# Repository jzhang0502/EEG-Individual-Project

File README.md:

# Electroencephalogram Device with Integrated Signal Processing for Daily Operations
## Author:
Yiyou Zhang

## About The Project 🧠:
This project aims to create an Electroencephalogram (EEG) system that records and utilises the user's neuroactivities, enabling the user to remotely activate a coffee machine with only the thoughts of wanting more coffee. It is advised, however, to consume caffeine in a responsible and moderate quantity.

## Milestones:
- [ ] Complete building functional EEG device
    - [x] Research on fundamental mechanisms of an EEG headset
    - [x] Identify and sketch out primary circuit elements
    - [x] Create schematic of EEG device on LTspice
    - [x] Source all required circuit components on DigiKey
    - [x] Complete project symbol library and overall schematic on KiCad
    - [ ] Complete PCB design on KiCad
    - [ ] Finish assembling all components on custom PCB and test out EEG device
- [ ] Perform signal processing and analysis on EEG data
- [ ] Create models capable of recognising specific EEG activities

## License:

Distributed under the MIT License. See `LICENSE.txt` for more information.

<p align="right">(<a href="#readme-top">back to top</a>)</p>

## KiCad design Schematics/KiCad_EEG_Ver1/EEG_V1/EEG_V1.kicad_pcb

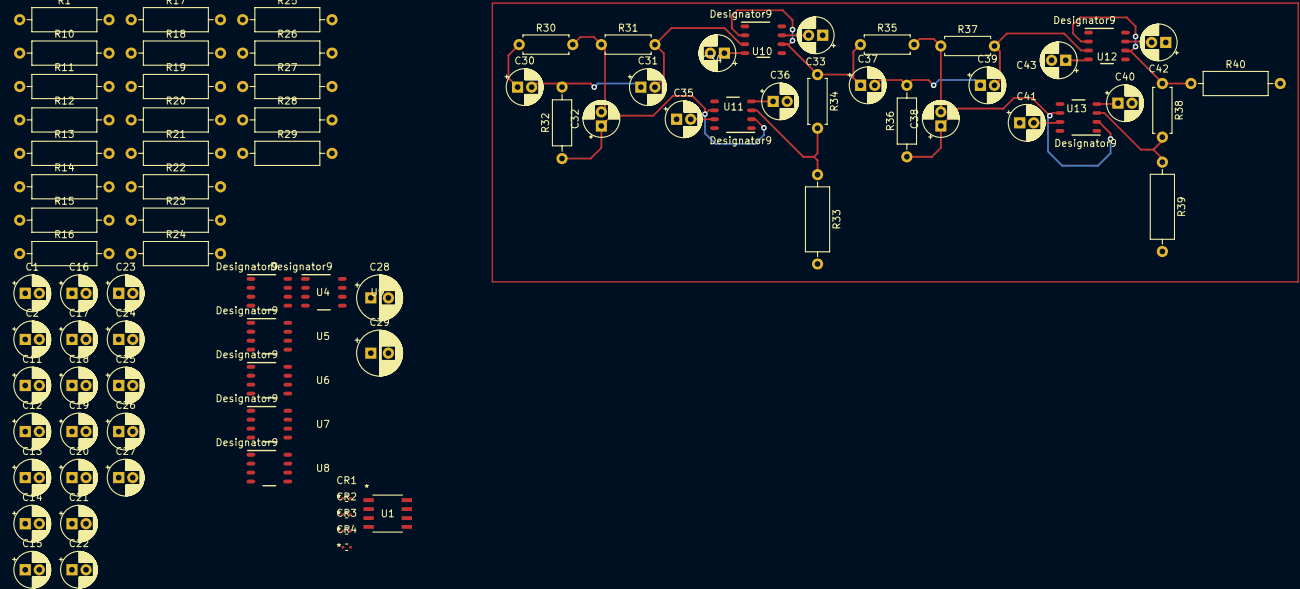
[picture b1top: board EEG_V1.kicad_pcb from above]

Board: 2 copper layers, 82 parts (0 on the bottom side), 35 nets.

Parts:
C1, C2, C14, C15, C16, C17, C19, C20, C22, C23, C24, C25, C26, C27, C30, C31, C33, C34, C35, C36, C37, C39, C40, C41, C42, C43: 0.1u; CP_Radial_D5.0mm_P2.00mm
C11, C21: 33n; CP_Radial_D5.0mm_P2.00mm
C12, C13, C18: 5.6n; CP_Radial_D5.0mm_P2.00mm
C28, C29: 10u; CP_Radial_D6.3mm_P2.50mm
C32, C38: 0.2u; CP_Radial_D5.0mm_P2.00mm
CR1, CR2, CR3, CR4: D5V0F1U2S9-7; CR_0F1U2S9-7_DIO
R1: 2k; R_Axial_DIN0309_L9.0mm_D3.2mm_P12.70mm_Horizontal
R10, R11, R26: 4.99k; R_Axial_DIN0309_L9.0mm_D3.2mm_P12.70mm_Horizontal
R12, R13: 22k; R_Axial_DIN0309_L9.0mm_D3.2mm_P12.70mm_Horizontal
R14, R15, R16, R18, R25, R28, R33, R39, R40: 10k; R_Axial_DIN0309_L9.0mm_D3.2mm_P12.70mm_Horizontal
R17: 499k; R_Axial_DIN0309_L9.0mm_D3.2mm_P12.70mm_Horizontal
R19, R22: 100k; R_Axial_DIN0309_L9.0mm_D3.2mm_P12.70mm_Horizontal
R20: 1.8k; R_Axial_DIN0309_L9.0mm_D3.2mm_P12.70mm_Horizontal
R21: 5.6k; R_Axial_DIN0309_L9.0mm_D3.2mm_P12.70mm_Horizontal
R23, R24, R27: 2.37k; R_Axial_DIN0309_L9.0mm_D3.2mm_P12.70mm_Horizontal
R29: R; R_Axial_DIN0309_L9.0mm_D3.2mm_P12.70mm_Horizontal
R30, R31, R35, R37: 32k; R_Axial_DIN0207_L6.3mm_D2.5mm_P7.62mm_Horizontal
R32, R36: 16k; R_Axial_DIN0207_L6.3mm_D2.5mm_P10.16mm_Horizontal
R34, R38: 250; R_Axial_DIN0207_L6.3mm_D2.5mm_P7.62mm_Horizontal
U1: INA819IDGK; INA819ID
U4, U5, U6, U7, U8, U9, U10, U11, U12, U13: OPA172IDR

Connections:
/Vout1: C21.1, R19.1, R20.2, U1.7, U6.3 (IN+)
DRL_in: R12.1, R13.1, U5.3 (IN+)
EEG_out: R28.2, U9.6 (OUT)
Inv_Summing_Amp_in: R23.2, R24.1, R27.1, U8.2 (IN-)
unnamed: C11.1, C12.1, CR2.2, CR4.1, R10.2, R15.1
unnamed: C11.2, C13.2, CR1.2, CR3.1, R11.2, R16.1
unnamed: C30.2, C31.1, R32.2
unnamed: C32.2, R30.2, R31.1
unnamed: C37.2, C39.1, R36.2
unnamed: C38.2, R35.2, R37.1
unnamed: R1.1, R12.2, U1.2 (Rg)
unnamed: R1.2, R13.2, U1.3 (Rg)
unnamed: R24.2, R25.2, R26.2
unnamed: R15.2, U1.4 (+)
unnamed: R16.2, U1.1 (-)
unnamed: C18.1, R14.2, R17.1, U4.2 (IN-)
unnamed: C18.2, R17.2, R18.1, U4.6 (OUT)
unnamed: R14.1, U5.2 (IN-), U5.6 (OUT)
unnamed: C21.2, R19.2, R21.1, U6.6 (OUT)
unnamed: R21.2, R22.1, U7.2 (IN-)
unnamed: R22.2, R23.1, U7.6 (OUT)
unnamed: R27.2, R29.1, U8.6 (OUT)
unnamed: R28.1, R29.2, U9.2 (IN-)
unnamed: C31.2, R31.2, U10.3 (IN+)
unnamed: C37.1, R34.1, R35.1, U10.2 (IN-), U10.6 (OUT)
unnamed: R33.1, R34.2, U11.3 (IN+)
unnamed: C32.1, R32.1, U11.2 (IN-), U11.6 (OUT)
unnamed: C39.2, R37.2, U12.3 (IN+)
unnamed: R38.1, R40.1, U12.2 (IN-), U12.6 (OUT)
unnamed: R38.2, R39.1, U13.3 (IN+)
unnamed: C38.1, R36.1, U13.2 (IN-), U13.6 (OUT)
Notch_in: C30.1, R30.1
Notch_out: C1.1, C2.2, C12.2, C13.1, C14.1, C15.2, C16.1, C17.2, C19.1, C20.2, C22.1, C23.2, C24.1, C25.2, C26.2, C27.1, C28.2, C29.1, C33.1, C34.2, C35.1, C36.2, C40.2, C41.1, C42.1, C43.2, R20.1, R25.1, R33.2, R39.2, R40.2, U1.6 (Ref), U4.3 (IN+), U7.3 (IN+), U8.3 (IN+), U9.3 (IN+)
V++: C1.2, C14.2, C16.2, C19.2, C22.2, C24.2, C27.2, C29.2, C33.2, C35.2, C41.2, C42.2, CR1.1, CR2.1, R26.1, U1.8 (V+), U4.7 (V+), U5.7 (V+), U6.7 (V+), U7.7 (V+), U8.7 (V+), U9.7 (V+), U10.7 (V+), U11.7 (V+), U12.7 (V+), U13.7 (V+)
V--: C2.1, C15.1, C17.1, C20.1, C23.1, C25.1, C26.1, C28.1, C34.1, C36.1, C40.1, C43.1, CR3.2, CR4.2, U1.5 (V-), U4.4 (V-), U5.4 (V-), U6.4 (V-), U7.4 (V-), U8.4 (V-), U9.4 (V-), U10.4 (V-), U11.4 (V-), U12.4 (V-), U13.4 (V-)

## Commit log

2024-01-02 Create README.md
    Added initial README file to set up repository
2024-01-02 Created .gitignore file for repo
2024-01-02 Added MIT LICENSE for repo
2024-01-02 Initial update to main README.txt
    Added project details, listed milestones and nested tasks
2024-01-02 Updated main README.txt milestone progress
    Completed researching, and sketching first overall circuit schematic on LTspice
2024-01-02 Initial sketch of EEG device gain stages
    The sketch includes the following:
    - 2x9V battery power source
    - INA819 inst amp with 21 gain
    - Non-inv op amp with 55.95 gain
    - Non-inv op amp with 18.86 gain
    - Total gain 22156
2024-01-02 Updated EEG_Schematic_LT
    Following additions:
    - Driven right leg circuit with gain 50
    - Added capacitor on stage 2 non-inv op amp as low-pass filter with Fc = 48Hz
    - Additional descriptions on circuit blocks
2024-01-02 Updated EEG_Schematic_LT.asc
    Following additions and alterations:
    - Added voltage source as "Electrode" that simulates electrode readings
    - Connected all parts of EEG circuit
    - Added optional high-pass filter to connect to inst amp
    - Changed inst amp gain to 22.10
    - Changed stage 2 non-inv op amp gain to 56.56
2024-01-02 Updated EEG_Schematic_LT.asc
    Following changes:
    - Changed stage 3 non-inv op amp gain to 17.86
    - Total gain is now 22322.82
2024-01-02 Updated EEG_Schematic_LT.asc
    Following changes:
    - Additional documentation to explain every circuit element
    - Stage 1 INA819 inst amp gain is 22.10
    - Stage 2 non-inv op amp gain is 56.56
    - Stage 3 inv op amp gain is -17.86
    - Stage 4 inv summing amp gain is -1 with offset 2.4969V
2024-01-05 Updated EEG_Schematic_LT.asc
    Added the following/
    - RFI filter with Fc = 445.4578Hz
    - ESD protection circuit with 4 diodes
2024-01-06 Uploaded KiCad Symbol Library
    Library includes imported symbols from DigiKey for corresponding circuit parts.
2024-01-06 Uploaded KiCad project files
    All created files for KiCad project, including schematics, pcb etc.
2024-01-06 Created Excel spreadsheet for circuit component listing
    Lists the following for every circuit component needed to order/
    - Value
    - Serial number
    - Quantity
    - Price
2024-01-08 Updated circuit_components spreadsheet
    Added newly selected op amp
2024-01-09 Updated spreadsheet & schematic
    Added the following/
    - Added chosen diode and op amp for components spreadsheet
    - Created schematic file in KiCad
    - Updated KiCad component library with added diode and op amp
2024-01-28 Updated KiCad project schematic & symbol library
    Changed diode choice to D5V0F1U2S9-7
    Total cost currently $39.85
2024-03-18 KiCad schematic mostly done
2024-03-19 Added notch filter 50Hz
2024-03-22 Schematic update
2024-04-07 Footprint update
2024-04-08 Twin rejection filter modeled
    This is a prelim layout but i definitely reckon i can squeeze the rectangular config of the two stages into more of a square config.

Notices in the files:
README.md:
License: MIT
